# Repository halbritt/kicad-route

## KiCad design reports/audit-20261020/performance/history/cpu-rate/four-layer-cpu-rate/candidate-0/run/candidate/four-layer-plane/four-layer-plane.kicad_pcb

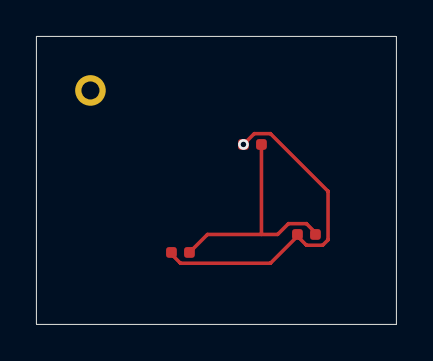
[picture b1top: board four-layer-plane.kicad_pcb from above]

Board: 4 copper layers, 20.0 x 16.0 mm, 4 parts (0 on the bottom side), 2 nets.

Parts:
J1: TP
R1, R2, R3: R_0402

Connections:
GND: J1.1, R1.1, R2.1, R3.1
SIG: R1.2, R2.2, R3.2
